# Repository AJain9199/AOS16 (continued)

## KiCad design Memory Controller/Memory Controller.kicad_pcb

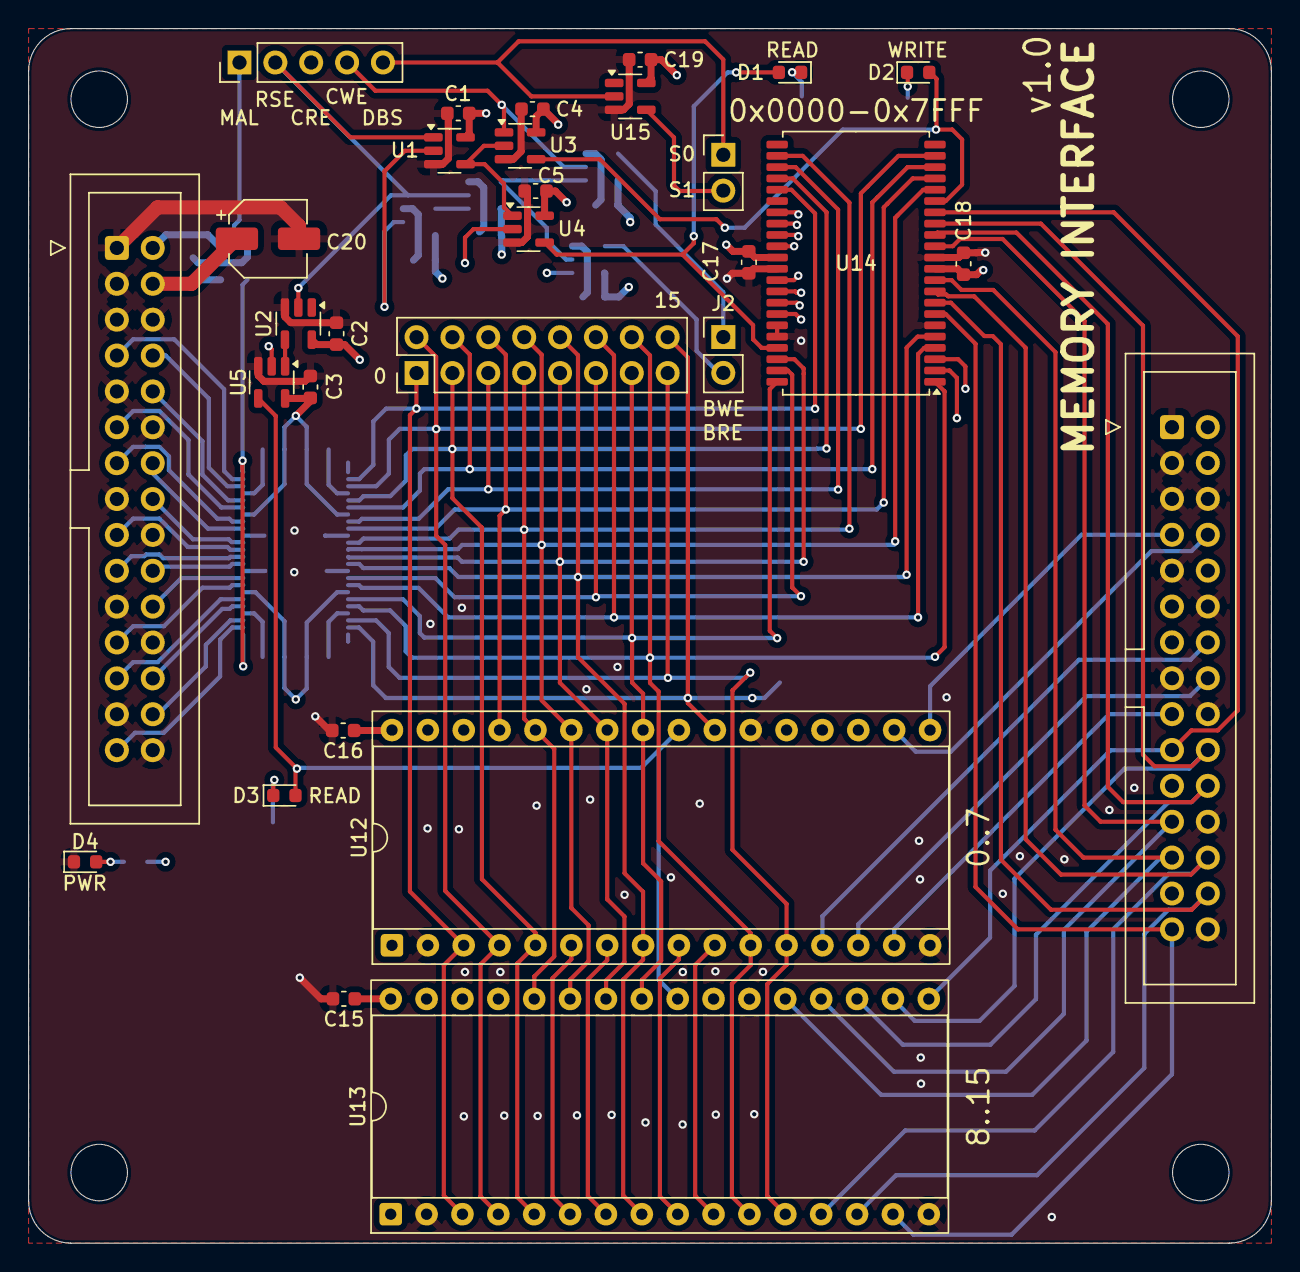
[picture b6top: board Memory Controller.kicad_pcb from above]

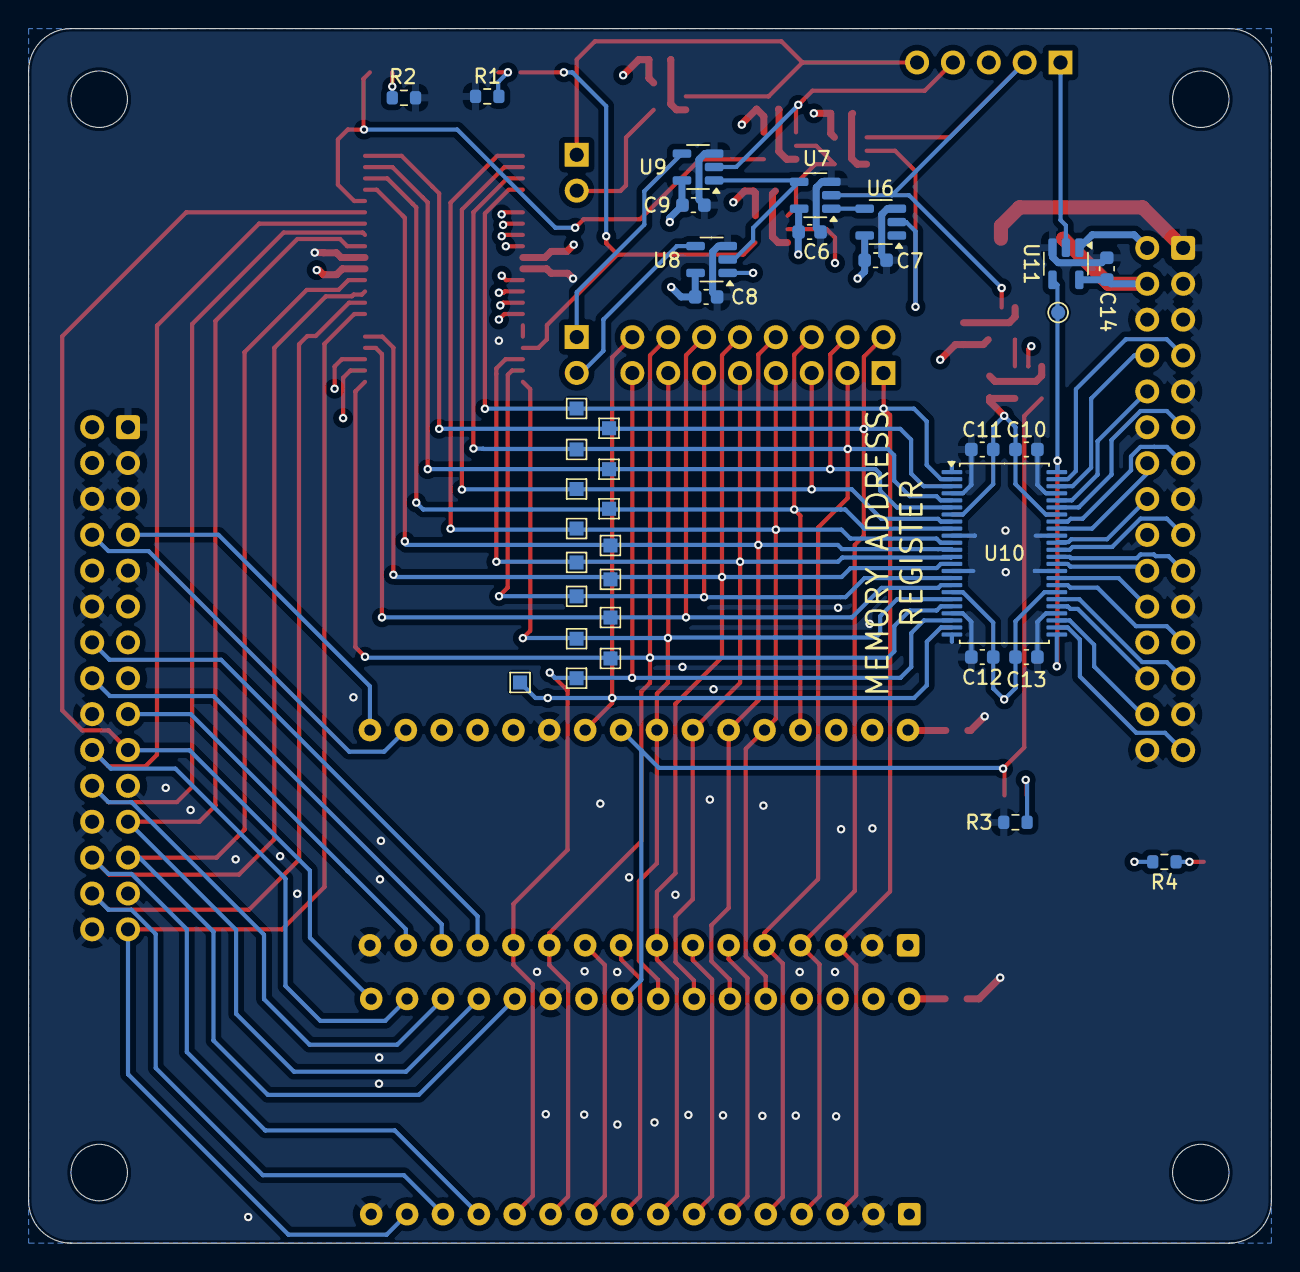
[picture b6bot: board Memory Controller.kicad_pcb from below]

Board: 4 copper layers, 88.0 x 86.0 mm, 70 parts (36 on the bottom side), 71 nets.

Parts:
C1, C2, C3, C4, C5, C6, C7, C8, C9, C15, C16, C19: C; C_0603_1608Metric
C10, C11, C12, C13: 0.01uF; C_0603_1608Metric
C14, C17, C18: 0.1uF; C_0603_1608Metric
C20: C; CP_Elec_5x5.3
D1, D2, D3, D4: LED; LED_0603_1608Metric
H1, H2, H3, H4: MountingHole; MountingHole_4mm
J1: Conn_01x05; PinHeader_1x05_P2.54mm_Vertical
J2, J6: Conn_01x02; PinHeader_1x02_P2.54mm_Vertical
J3, J5: Conn_02x15_Odd_Even; IDC-Header_2x15_P2.54mm_Vertical
J4: Conn_02x08_Top_Bottom; PinHeader_2x08_P2.54mm_Vertical
R1, R2, R3, R4: R; R_0603_1608Metric
TP1: TestPoint; TestPoint_Pad_D1.0mm
TP2, TP3, TP4, TP5, TP6, TP7, TP8, TP9, TP10, TP11, TP12, TP13, TP14, TP15, TP16, TP17: TestPoint_Small; TestPoint_Pad_1.0x1.0mm
U1, U3, U4, U5, U7, U8, U9: 74AHC1G32; SOT-23-5
U2, U6, U15: 74AHC1G04; SOT-23-5
U10: SN74AHCT16374DGGR; TSSOP-48_6.1x12.5mm_P0.5mm
U11: 74AHC1G08; SOT-23-5
U12, U13: SST39SF010; DIP-32_W15.24mm_Socket
U14: 71016S12PHG8; TSOP-II-44_10.16x18.41mm_P0.8mm

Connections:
+5V: C1.1, C2.1, C3.1, C4.1, C5.1, C6.1, C7.1, C8.1, C9.1, C10.1, C11.1, C12.1, C13.1, C14.1, C15.1, C16.1, C17.1, C18.1, C19.1, C20.1, J3.4, R4.2, U1.5 (VCC), U2.5 (VCC), U3.5 (VCC), U4.5 (VCC), U5.5 (VCC), U6.5 (VCC), U7.5 (VCC), U8.5 (VCC), U9.5 (VCC), U10.7 (VCC_1), U10.18 (VCC_2), U10.31 (VCC), U10.42 (VCC_4), U11.5 (VCC), U12.31 (PGM), U12.32 (VCC), U13.31 (PGM), U13.32 (VCC), U14.11 (VCC_1), U14.33 (VCC_2), U15.5 (VCC)
/BRE: J2.2, U8.4
/BWE: J2.1, U9.4
/CLK: J3.2, U11.1
/CRE: J1.3, U4.2, U5.2, U8.1
/CWE: J1.4, U3.1, U9.2
/DBS: J1.5, J6.1, U15.2
/MAL: J1.1, U11.2
/ROM/DATA0: J5.7, U12.17 (D3), U14.29 (I/O_8)
/ROM/DATA1: J5.8, U12.18 (D4), U14.30 (I/O_9)
/ROM/DATA2: J5.10, U12.19 (D5), U14.31 (I/O_10)
/ROM/DATA3: J5.11, U12.20 (D6), U14.32 (I/O_11)
/ROM/DATA4: J5.13, U12.21 (D7), U14.35 (I/O_12)
/ROM/DATA5: J5.14, U12.13 (D0), U14.36 (I/O_13)
/ROM/DATA6: J5.16, U12.14 (D1), U14.37 (I/O_14)
/ROM/DATA7: J5.17, U12.15 (D2), U14.38 (I/O_15)
/ROM/DATA8: J5.19, U13.17 (D3), U14.16 (I/O_7)
/ROM/DATA9: J5.20, U13.18 (D4), U14.15 (I/O_6)
/ROM/DATA10: J5.22, U13.19 (D5), U14.14 (I/O_5)
/ROM/DATA11: J5.23, U13.20 (D6), U14.13 (I/O_4)
/ROM/DATA12: J5.25, U13.21 (D7), U14.10 (I/O_3)
/ROM/DATA13: J5.26, U13.13 (D0), U14.9 (I/O_2)
/ROM/DATA14: J5.28, U13.14 (D1), U14.8 (I/O_1)
/ROM/DATA15: J5.29, U13.15 (D2), U14.7 (I/O_0)
/RSE: J1.2, U1.1, U2.2, U7.2
/S1: J6.2, U15.4
/bus_conn/IO0: J3.7, U10.47 (1D1)
/bus_conn/IO1: J3.8, U10.46 (1D2)
/bus_conn/IO2: J3.10, U10.44 (1D3)
/bus_conn/IO3: J3.11, U10.43 (1D4)
/bus_conn/IO4: J3.13, U10.41 (1D5)
/bus_conn/IO5: J3.14, U10.40 (1D6)
/bus_conn/IO6: J3.16, U10.38 (1D7)
/bus_conn/IO7: J3.17, U10.37 (1D8)
/bus_conn/IO8: J3.19, U10.36 (2D1)
/bus_conn/IO9: J3.20, U10.35 (2D2)
/bus_conn/IO10: J3.22, U10.33 (2D3)
/bus_conn/IO11: J3.23, U10.32 (2D4)
/bus_conn/IO12: J3.25, U10.30 (2D5)
/bus_conn/IO13: J3.26, U10.29 (2D6)
/bus_conn/IO14: J3.28, U10.27 (2D7)
/bus_conn/IO15: J3.29, U10.26 (2D8)
/word_conn/IN0: J4.1, TP2.1, U10.2 (1Q1), U12.3 (A15), U13.3 (A15), U14.27 (A8)
/word_conn/IN1: J4.2, TP3.1, U10.3 (1Q2), U12.4 (A12), U13.4 (A12), U14.21 (A12)
/word_conn/IN2: J4.3, TP4.1, U10.5 (1Q3), U12.5 (A7), U13.5 (A7), U14.26 (A9)
/word_conn/IN3: J4.4, TP5.1, U10.6 (1Q4), U12.6 (A6), U13.6 (A6), U14.20 (A13)
/word_conn/IN4: J4.5, TP6.1, U10.8 (1Q5), U12.7 (A5), U13.7 (A5), U14.25 (A10)
/word_conn/IN5: J4.6, TP7.1, U10.9 (1Q6), U12.29 (A14), U13.29 (A14), U14.19 (A14)
/word_conn/IN6: J4.7, TP8.1, U10.11 (1Q7), U12.28 (A13), U13.28 (A13), U14.24 (A11)
/word_conn/IN7: J4.8, TP9.1, U10.12 (1Q8), U12.27 (A8), U13.27 (A8), U14.18 (A15)
/word_conn/IN8: J4.9, TP10.1, U10.13 (2Q1), U12.26 (A9), U13.26 (A9), U14.42 (A7)
/word_conn/IN9: J4.10, TP11.1, U10.14 (2Q2), U12.8 (A4), U13.8 (A4), U14.5 (A0)
/word_conn/IN10: J4.11, TP12.1, U10.16 (2Q3), U12.9 (A3), U13.9 (A3), U14.43 (A6)
/word_conn/IN11: J4.12, TP13.1, U10.17 (2Q4), U12.10 (A2), U13.10 (A2), U14.4 (A1)
/word_conn/IN12: J4.13, TP14.1, U10.19 (2Q5), U12.25 (A11), U13.25 (A11), U14.44 (A5)
/word_conn/IN13: J4.14, TP15.1, U10.20 (2Q6), U12.11 (A1), U13.11 (A1), U14.1 (A4)
/word_conn/IN14: J4.15, TP16.1, U10.22 (2Q7), U12.12 (A0), U13.12 (A0), U14.3 (A2)
/word_conn/IN15: J4.16, TP17.1, U1.2, U6.2, U10.23 (2Q8), U12.23 (A10), U13.23 (A10), U14.2 (A3)
/~RAM_RE: D1.2 (A), U4.4, U14.41 (~OE)
/~RAM_WE: D2.2 (A), U3.4, U14.17 (~WE)
/~ROM_RE: D3.2 (A), U5.4, U12.24 (OE), U13.24 (OE)
GND: C1.2, C2.2, C3.2, C4.2, C5.2, C6.2, C7.2, C8.2, C9.2, C10.2, C11.2, C12.2, C13.2, C14.2, C15.2, C16.2, C17.2, C18.2, C19.2, C20.2, D4.1 (K), J3.1, J3.3, J3.5, J3.6, J3.9, J3.12, J3.15, J3.18, J3.21, J3.24, J3.27, J3.30, J5.1, J5.3, J5.5, J5.6, J5.9, J5.12, J5.15, J5.18, J5.21, J5.24, J5.27, J5.30, R1.1, R2.1, R3.1, U1.3 (GND), U2.3 (GND), U3.3 (GND), U4.3 (GND), U5.3 (GND), U6.3 (GND), U7.3 (GND), U8.3 (GND), U9.3 (GND), U10.1 (1~OE), U10.4 (GND_1), U10.10 (GND_2), U10.15 (GND_3), U10.21 (GND_4), U10.24 (2~OE), U10.28 (GND), U10.34 (GND_6), U10.39 (GND_7), U10.45 (GND_8), U11.3 (GND), U12.2 (A16), U12.16 (GND), U12.22 (CE), U13.2 (A16), U13.16 (GND), U13.22 (CE), U14.6 (~CS), U14.12 (VSS_1), U14.34 (VSS_2), U14.39 (~BLE), U14.40 (~BHE), U15.3 (GND)
unnamed: D1.1 (K), R1.2
unnamed: D2.1 (K), R2.2
unnamed: D3.1 (K), R3.2
unnamed: D4.2 (A), R4.1
unnamed: U1.4, U3.2, U4.1
unnamed: U2.4, U5.1
unnamed: U6.4, U7.1
unnamed: U7.4, U8.2, U9.1
unnamed: TP1.1, U10.25 (2CLK), U10.48 (1CLK), U11.4

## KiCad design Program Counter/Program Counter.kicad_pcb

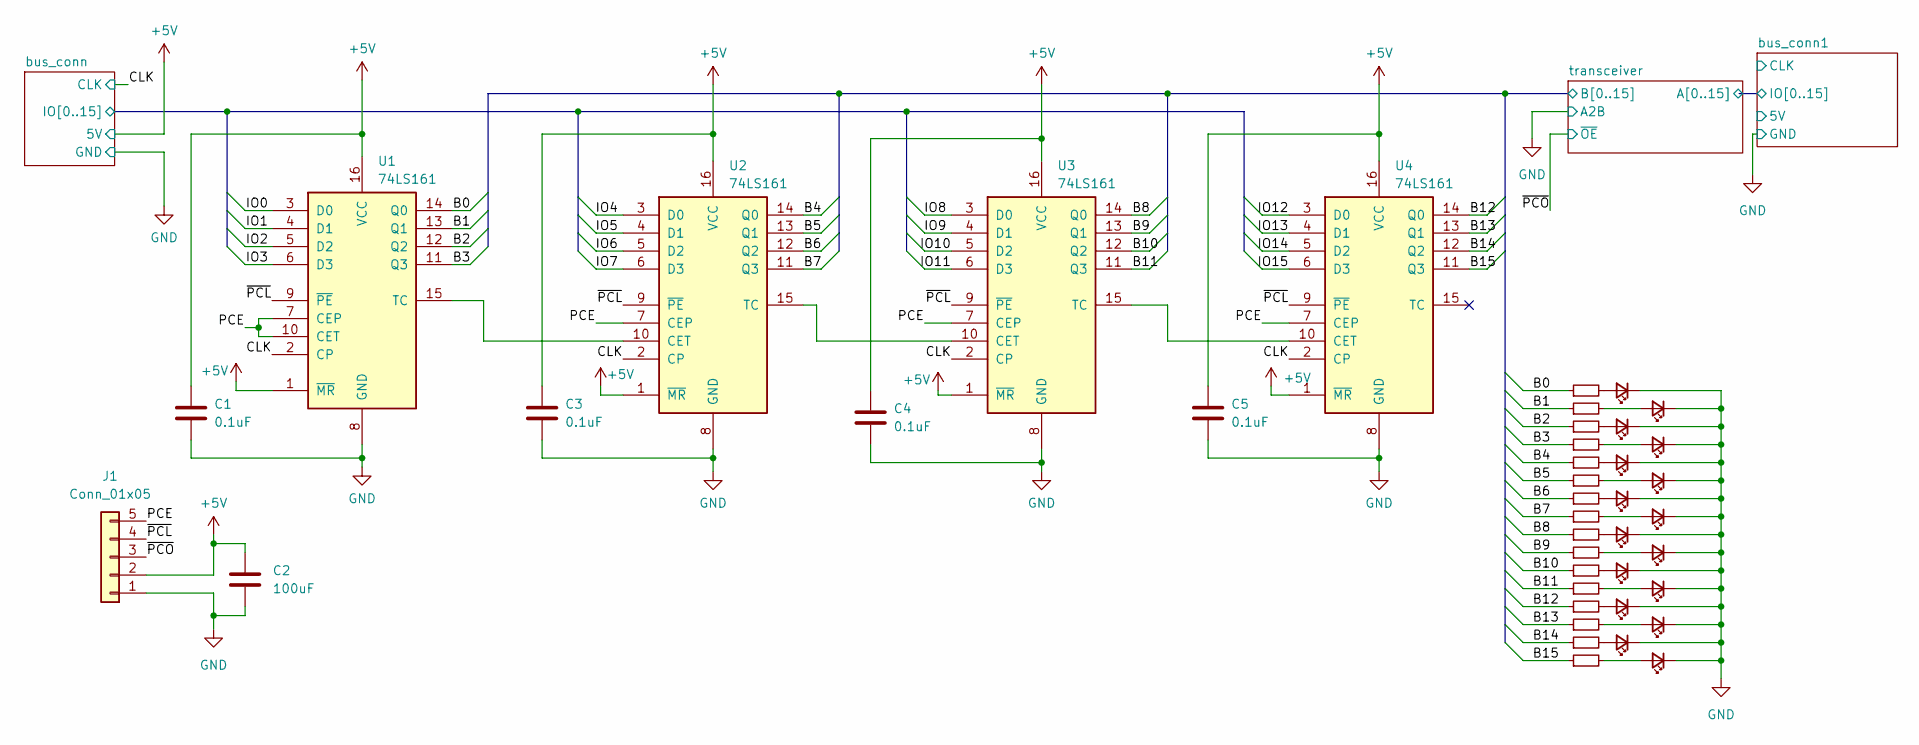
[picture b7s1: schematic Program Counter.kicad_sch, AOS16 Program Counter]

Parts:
C1, C3, C4, C5: 0.1uF; C_0603_1608Metric
C2: 100uF; CP_Elec_5x5.3
D1, D2, D3, D4, D5, D6, D7, D8, D9, D10, D11, D12, D13, D14, D15, D16: LED_Small; LED_0603_1608Metric
J1: Conn_01x05; PinHeader_1x05_P2.54mm_Vertical
R2, R3, R4, R5, R6, R7, R8, R9, R10, R11, R12, R13, R14, R15, R16, R17: 220; R_0603_1608Metric
U1, U2, U3, U4: 74LS161; SOIC-16_4.55x10.3mm_P1.27mm

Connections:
/CLK: U1.2 (CP), U2.2 (CP), U3.2 (CP), U4.2 (CP); also elsewhere on the board
/PCE: J1.5, U1.7 (CEP), U1.10 (CET), U2.7 (CEP), U3.7 (CEP), U4.7 (CEP)
/bus_conn/IO0: U1.3 (D0); also elsewhere on the board
/bus_conn/IO1: U1.4 (D1); also elsewhere on the board
/bus_conn/IO2: U1.5 (D2); also elsewhere on the board
/bus_conn/IO3: U1.6 (D3); also elsewhere on the board
/bus_conn/IO4: U2.3 (D0); also elsewhere on the board
/bus_conn/IO5: U2.4 (D1); also elsewhere on the board
/bus_conn/IO6: U2.5 (D2); also elsewhere on the board
/bus_conn/IO7: U2.6 (D3); also elsewhere on the board
/bus_conn/IO8: U3.3 (D0); also elsewhere on the board
/bus_conn/IO9: U3.4 (D1); also elsewhere on the board
/bus_conn/IO10: U3.5 (D2); also elsewhere on the board
/bus_conn/IO11: U3.6 (D3); also elsewhere on the board
/bus_conn/IO12: U4.3 (D0); also elsewhere on the board
/bus_conn/IO13: U4.4 (D1); also elsewhere on the board
/bus_conn/IO14: U4.5 (D2); also elsewhere on the board
/bus_conn/IO15: U4.6 (D3); also elsewhere on the board
/transceiver/B0: R2.1, U1.14 (Q0); also elsewhere on the board
/transceiver/B1: R3.1, U1.13 (Q1); also elsewhere on the board
/transceiver/B2: R4.1, U1.12 (Q2); also elsewhere on the board
/transceiver/B3: R5.1, U1.11 (Q3); also elsewhere on the board
/transceiver/B4: R6.1, U2.14 (Q0); also elsewhere on the board
/transceiver/B5: R7.1, U2.13 (Q1); also elsewhere on the board
/transceiver/B7: R9.1, U2.11 (Q3); also elsewhere on the board
/transceiver/B8: R10.1, U3.14 (Q0); also elsewhere on the board
/transceiver/B9: R11.1, U3.13 (Q1); also elsewhere on the board
/transceiver/B10: R12.1, U3.12 (Q2); also elsewhere on the board
/transceiver/B11: R13.1, U3.11 (Q3); also elsewhere on the board
/transceiver/B12: R14.1, U4.14 (Q0); also elsewhere on the board
/transceiver/B13: R15.1, U4.13 (Q1); also elsewhere on the board
/transceiver/B14: R16.1, U4.12 (Q2); also elsewhere on the board
/transceiver/B15: R17.1, U4.11 (Q3); also elsewhere on the board
/~PCL: J1.4, U1.9 (~PE), U2.9 (~PE), U3.9 (~PE), U4.9 (~PE)
GND: C1.2, C2.2, C3.2, C4.2, C5.2, D1.1 (K), D2.1 (K), D3.1 (K), D4.1 (K), D5.1 (K), D6.1 (K), D7.1 (K), D8.1 (K), D9.1 (K), D10.1 (K), D11.1 (K), D12.1 (K), D13.1 (K), D14.1 (K), D15.1 (K), D16.1 (K), J1.1, U1.8 (GND), U2.8 (GND), U3.8 (GND), U4.8 (GND); also elsewhere on the board
unnamed: D1.2 (A), R2.2
unnamed: D2.2 (A), R4.2
unnamed: D3.2 (A), R6.2
unnamed: D5.2 (A), R10.2
unnamed: D6.2 (A), R12.2
unnamed: D7.2 (A), R14.2
unnamed: D8.2 (A), R16.2
unnamed: D9.2 (A), R3.2
unnamed: D10.2 (A), R5.2
unnamed: D11.2 (A), R7.2
unnamed: D12.2 (A), R9.2
unnamed: D13.2 (A), R11.2
unnamed: D14.2 (A), R13.2
unnamed: D15.2 (A), R15.2
unnamed: D16.2 (A), R17.2
unnamed: U1.15 (TC), U2.10 (CET)
unnamed: U2.15 (TC), U3.10 (CET)
unnamed: U3.15 (TC), U4.10 (CET)

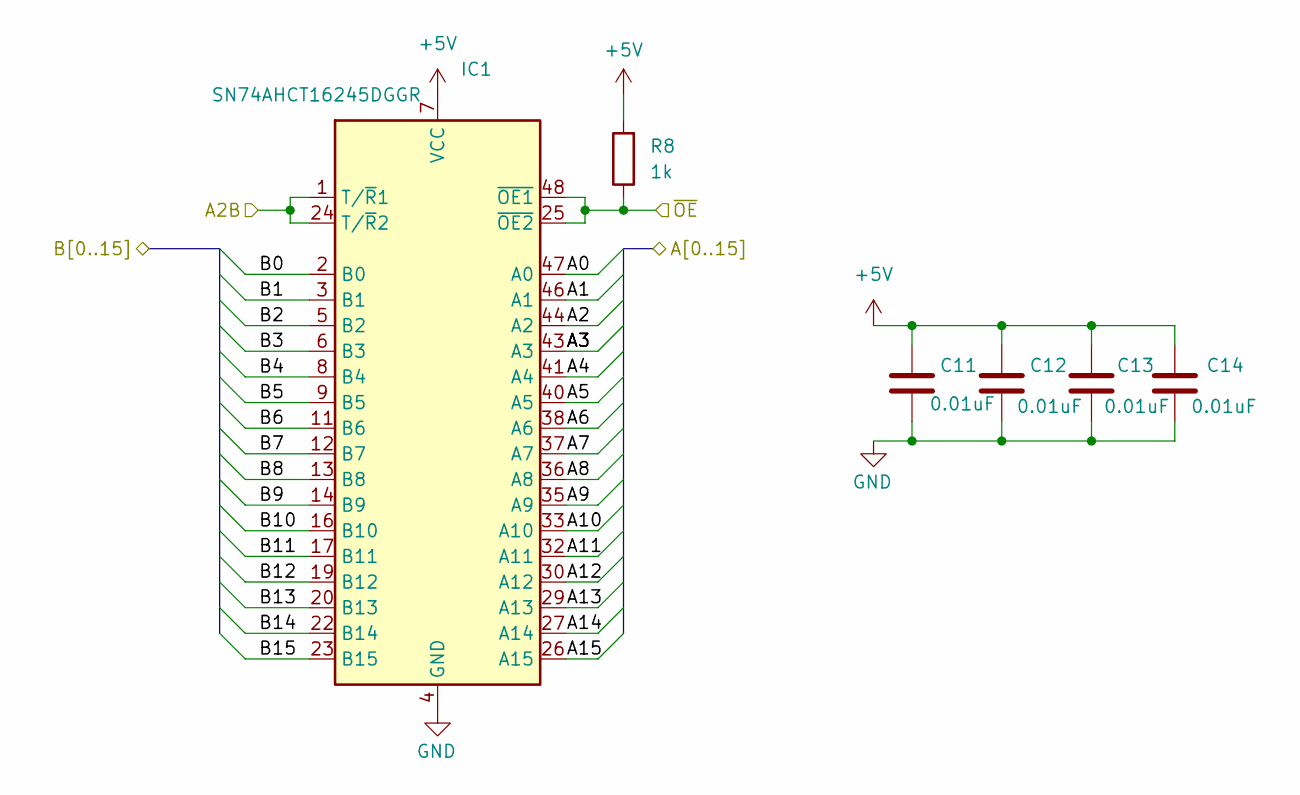
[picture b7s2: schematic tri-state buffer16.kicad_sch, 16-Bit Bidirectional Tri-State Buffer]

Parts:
C11, C12, C13, C14: 0.01uF; C_0603_1608Metric
IC1: SN74AHCT16245DGGR; TSSOP-48_6.1x12.5mm_P0.5mm
R8: 1k; R_0603_1608Metric

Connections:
/bus_conn1/IO0: IC1.47 (A0); also elsewhere on the board
/bus_conn1/IO1: IC1.46 (A1); also elsewhere on the board
/bus_conn1/IO2: IC1.44 (A2); also elsewhere on the board
/bus_conn1/IO3: IC1.43 (A3); also elsewhere on the board
/bus_conn1/IO4: IC1.41 (A4); also elsewhere on the board
/bus_conn1/IO5: IC1.40 (A5); also elsewhere on the board
/bus_conn1/IO6: IC1.38 (A6); also elsewhere on the board
/bus_conn1/IO7: IC1.37 (A7); also elsewhere on the board
/bus_conn1/IO8: IC1.36 (A8); also elsewhere on the board
/bus_conn1/IO9: IC1.35 (A9); also elsewhere on the board
/bus_conn1/IO10: IC1.33 (A10); also elsewhere on the board
/bus_conn1/IO11: IC1.32 (A11); also elsewhere on the board
/bus_conn1/IO12: IC1.30 (A12); also elsewhere on the board
/bus_conn1/IO13: IC1.29 (A13); also elsewhere on the board
/bus_conn1/IO14: IC1.27 (A14); also elsewhere on the board
/bus_conn1/IO15: IC1.26 (A15); also elsewhere on the board
/transceiver/B0: IC1.2 (B0); also elsewhere on the board
/transceiver/B1: IC1.3 (B1); also elsewhere on the board
/transceiver/B2: IC1.5 (B2); also elsewhere on the board
/transceiver/B3: IC1.6 (B3); also elsewhere on the board
/transceiver/B4: IC1.8 (B4); also elsewhere on the board
/transceiver/B5: IC1.9 (B5); also elsewhere on the board
/transceiver/B7: IC1.12 (B7); also elsewhere on the board
/transceiver/B8: IC1.13 (B8); also elsewhere on the board
/transceiver/B9: IC1.14 (B9); also elsewhere on the board
/transceiver/B10: IC1.16 (B10); also elsewhere on the board
/transceiver/B11: IC1.17 (B11); also elsewhere on the board
/transceiver/B12: IC1.19 (B12); also elsewhere on the board
/transceiver/B13: IC1.20 (B13); also elsewhere on the board
/transceiver/B14: IC1.22 (B14); also elsewhere on the board
/transceiver/B15: IC1.23 (B15); also elsewhere on the board
GND: C11.2, C12.2, C13.2, C14.2, IC1.1 (T/~R1), IC1.4 (GND), IC1.10 (GND), IC1.15 (GND), IC1.21 (GND), IC1.24 (T/~R2), IC1.28 (GND), IC1.34 (GND), IC1.39 (GND), IC1.45 (GND); also elsewhere on the board

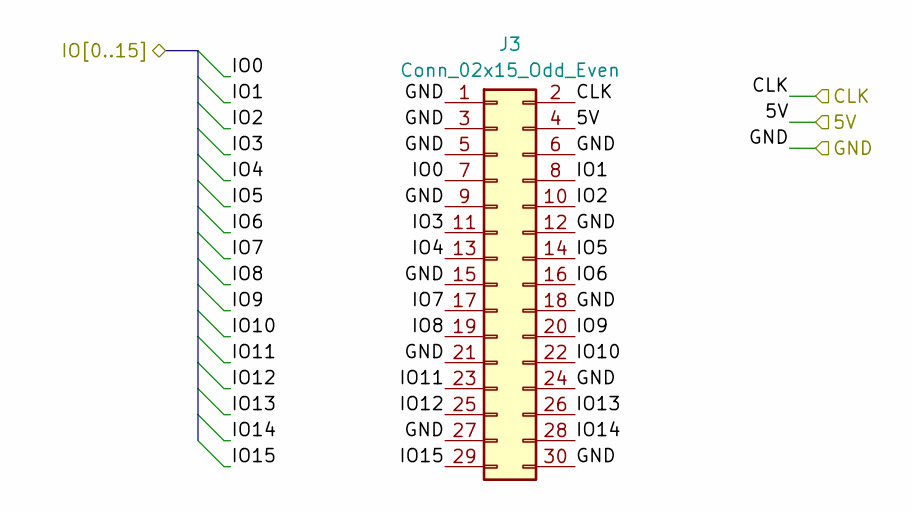
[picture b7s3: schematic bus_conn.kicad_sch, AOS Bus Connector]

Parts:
J3: Conn_02x15_Odd_Even; IDC-Header_2x15_P2.54mm_Vertical

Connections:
/bus_conn1/5V: J3.4
/bus_conn1/CLK: J3.2
/bus_conn1/IO0: J3.7; also elsewhere on the board
/bus_conn1/IO1: J3.8; also elsewhere on the board
/bus_conn1/IO2: J3.10; also elsewhere on the board
/bus_conn1/IO3: J3.11; also elsewhere on the board
/bus_conn1/IO4: J3.13; also elsewhere on the board
/bus_conn1/IO5: J3.14; also elsewhere on the board
/bus_conn1/IO6: J3.16; also elsewhere on the board
/bus_conn1/IO7: J3.17; also elsewhere on the board
/bus_conn1/IO8: J3.19; also elsewhere on the board
/bus_conn1/IO9: J3.20; also elsewhere on the board
/bus_conn1/IO10: J3.22; also elsewhere on the board
/bus_conn1/IO11: J3.23; also elsewhere on the board
/bus_conn1/IO12: J3.25; also elsewhere on the board
/bus_conn1/IO13: J3.26; also elsewhere on the board
/bus_conn1/IO14: J3.28; also elsewhere on the board
/bus_conn1/IO15: J3.29; also elsewhere on the board
GND: J3.1, J3.3, J3.5, J3.6, J3.9, J3.12, J3.15, J3.18, J3.21, J3.24, J3.27, J3.30; also elsewhere on the board

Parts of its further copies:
J2: Conn_02x15_Odd_Even; IDC-Header_2x15_P2.54mm_Vertical

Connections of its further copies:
/CLK: J2.2; also elsewhere on the board
/bus_conn/IO0: J2.7; also elsewhere on the board
/bus_conn/IO1: J2.8; also elsewhere on the board
/bus_conn/IO2: J2.10; also elsewhere on the board
/bus_conn/IO3: J2.11; also elsewhere on the board
/bus_conn/IO4: J2.13; also elsewhere on the board
/bus_conn/IO5: J2.14; also elsewhere on the board
/bus_conn/IO6: J2.16; also elsewhere on the board
/bus_conn/IO7: J2.17; also elsewhere on the board
/bus_conn/IO8: J2.19; also elsewhere on the board
/bus_conn/IO9: J2.20; also elsewhere on the board
/bus_conn/IO10: J2.22; also elsewhere on the board
/bus_conn/IO11: J2.23; also elsewhere on the board
/bus_conn/IO12: J2.25; also elsewhere on the board
/bus_conn/IO13: J2.26; also elsewhere on the board
/bus_conn/IO14: J2.28; also elsewhere on the board
/bus_conn/IO15: J2.29; also elsewhere on the board
GND: J2.1, J2.3, J2.5, J2.6, J2.9, J2.12, J2.15, J2.18, J2.21, J2.24, J2.27, J2.30; also elsewhere on the board

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
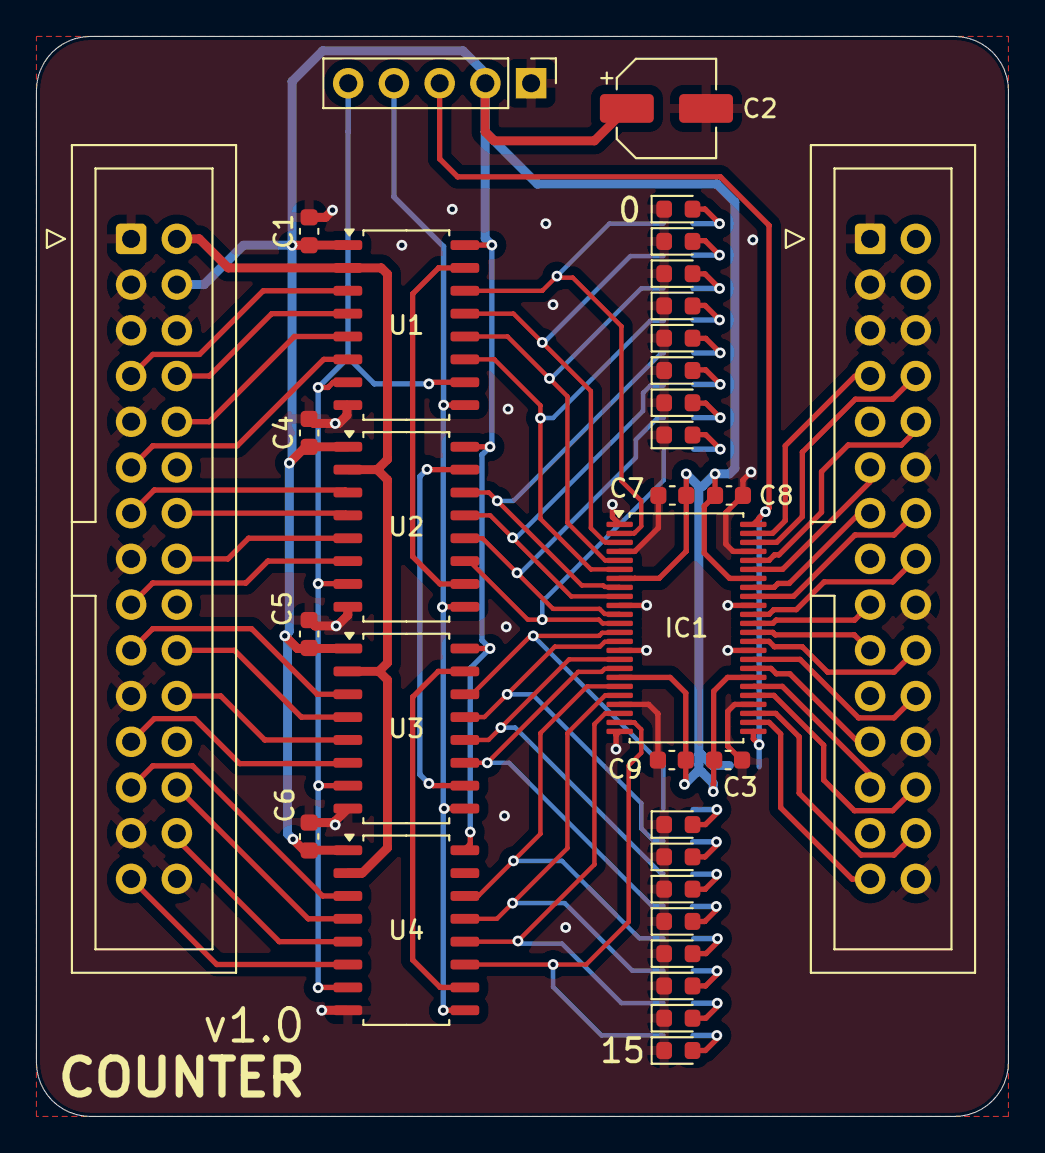
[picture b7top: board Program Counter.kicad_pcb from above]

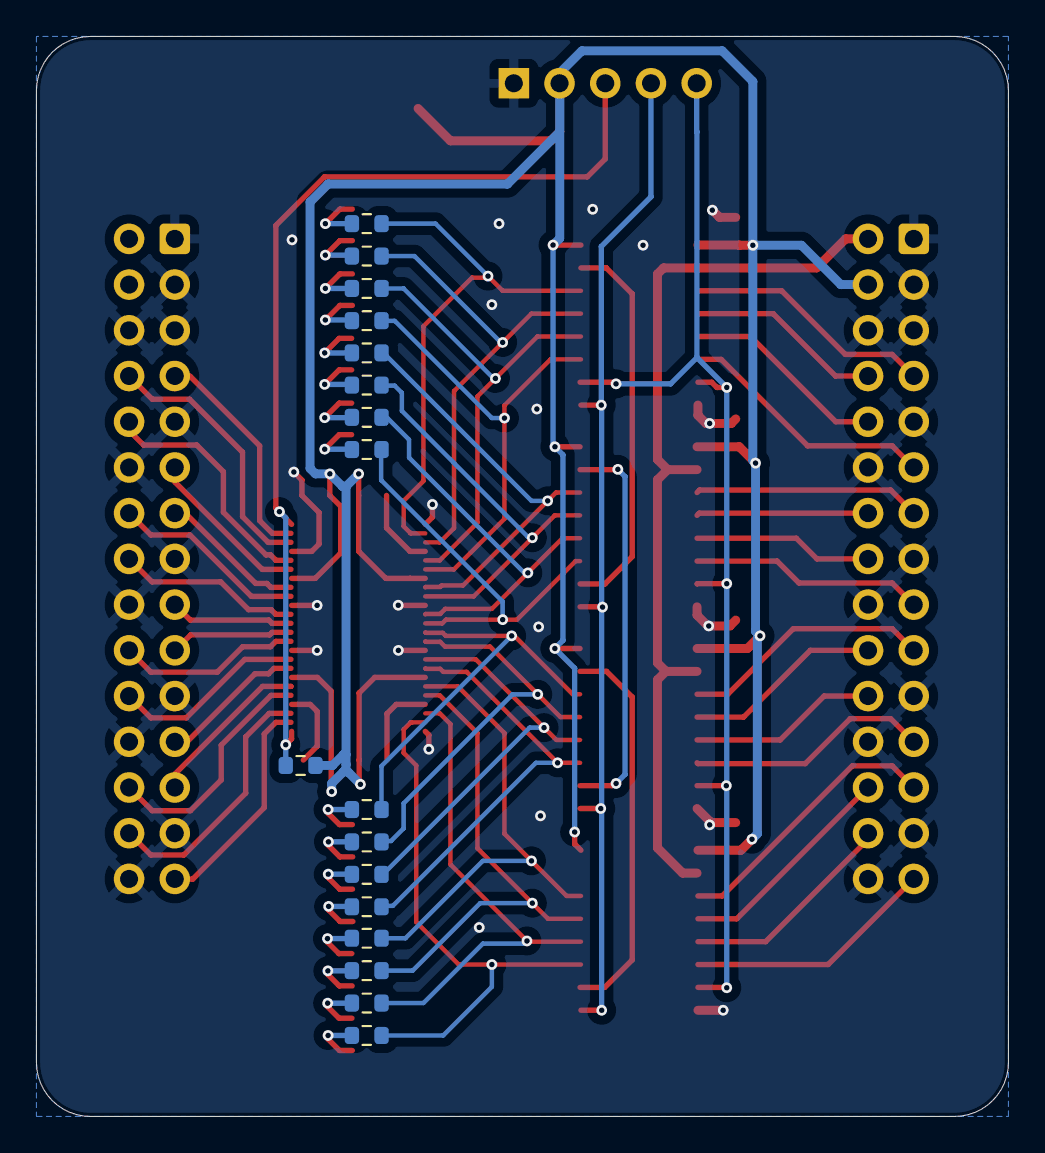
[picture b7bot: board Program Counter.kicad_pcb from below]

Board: 2 copper layers, 54.0 x 60.0 mm, 50 parts (17 on the bottom side), 73 nets.

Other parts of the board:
C6, C7, C8, C9: 0.01uF; C_0603_1608Metric
R18: 1k; R_0603_1608Metric

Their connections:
GND: C6.2, C7.2, C8.2, C9.2; also elsewhere on the board

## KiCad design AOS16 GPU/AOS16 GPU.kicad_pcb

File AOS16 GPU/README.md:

# AOS16 GPU

<h6 align="center">
GPU Front
</h6>

<h6 align="center">
GPU Back
</h6>

```mermaid
flowchart LR
    subgraph sub4 ["HCounter"]
        E["Counters"]
        F["Sync Comparator"]
        G["nOE Comparator"]
    end
    subgraph sub6 ["VCounter"]
        H["Counters"]
        I["Sync Comparator"]
        J["nOE Comparator"]
    end
    A[/"ADDR[0..14]"/]
    B[/"DATA[0..14]"/]
    C[["Digital-to-Analog<br/>Converter"]]
    D[/"VGA Output"/]
    K["NAND"]
    L(("nOE"))
    M(("CLK"))
    B --> C
    C -->|"RGB"| D
    E -->|"[0..7]"| A
    E --> F
    E --> G
    F -->|"HSync"| D
    H --> I
    H --> J
    I -->|"VSync"| D
    H -->|"[8..14]"| A
    G --> K
    J --> K
    K --> L
    M --> E
    M --> H
    %% mermaid-flow:pos E=333,36,76,32 F=467,104 G=465,161 H=668,45,80,32 I=815,97 J=816,158 A=115,260 B=101,362 C=298,363 D=561,403 K=595,264 L=820,341 M=77,55,101,60
```

## VGA Signal Generation
The board generates the SXGA 640x480@85Hz video mode. Each pixel is repeated 4 times across both axes for an effective resolution of 160x120. 

| Value                    | Frequency           |
| ------------------------ | ------------------- |
| Screen refresh rate      | 85 Hz               |
| Vertical refresh         | 43.269230769231 kHz |
| Pixel frequency          | 36.0 MHz            |
| **Clock frequency used** | **9.0 MHz**         |

It works by using counters for both the horizontal and vertical scanlines. The sync and output signals are set and unset at specific trigger counter values. 

### Horizontal Timing
2 [74hc161](../datasheets/sn74hc161.pdf)s are used to count the effective pixels. A quarter of the clock frequency (36/4 = 9 MHz) is used with the effective values to match the expected signal timings. Every line ending is used as the clock signal of the vertical counting circuit.

The 7 lower bits of the counter are used as ADDR\[0..7].

| Scanline Part         | Pixels | Effective Pixels | Time (µs) |
| --------------------- | ------ | ---------------- | --------- |
| Visible Area          | 640    | 120              | 17.777    |
| Front Porch           | 56     | 14               | 1.555     |
| Sync Pulse (inverted) | 56     | 14               | 1.555     |
| Back Porch            | 80     | 20               | 2.222     |
| Whole Line            | 832    | 208              | 23.111    |

### Vertical Timing
3 hc161s are used to count the actual lines. Bits \[2..8] are forwarded as the vertical address to ADDR\[8..14], effectively repeating each pixel 4 times.

| Frame Part   | Lines | Time (ms) |
| ------------ | ----- | --------- |
| Visible Area | 480   | 11.09333  |
| Front Porch  | 1     | 0.02311   |
| Sync Pulse   | 3     | 0.06933   |
| Back Porch   | 25    | 0.577     |
| Full Frame   | 509   | 11.76355  |
|              |       |           |
## Linear Framebuffer Mapping

| Dimension  | Value          |
| ---------- | -------------- |
| Width      | 160px          |
| Height     | 120px          |
| Pitch      | 256 words      |
| Depth      | 5 bits / color |
| Pixelwidth | 1 word         |
```c
uint16_t *pixel = 0x7FFF + y*pitch + x
```

## Test Video

https://github.com/user-attachments/assets/5f555ebd-57f7-4c56-b4e2-e7593a60e567

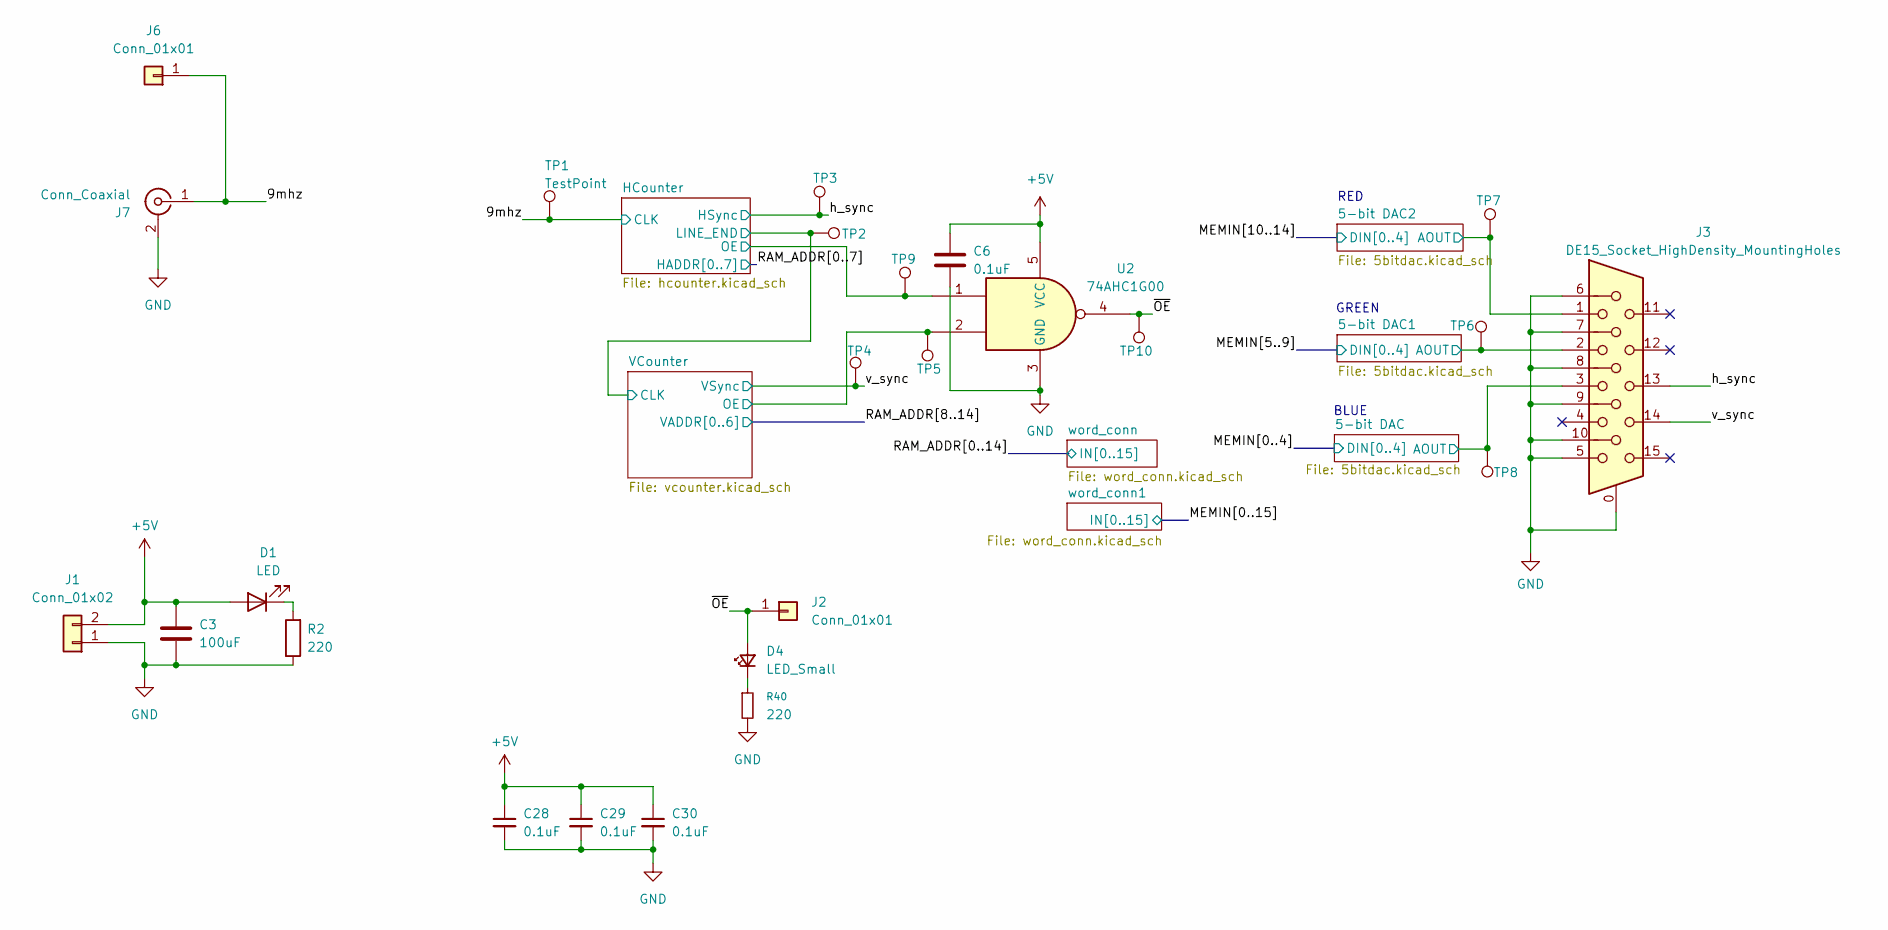
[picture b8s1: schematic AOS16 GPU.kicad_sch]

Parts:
C3: 100uF; CP_Elec_5x5.3
C6, C28, C29, C30: 0.1uF; C_0603_1608Metric
D1: LED; LED_0603_1608Metric
D4: LED_Small; LED_0603_1608Metric
J1: Conn_01x02; PinHeader_1x02_P2.54mm_Vertical
J2, J6: Conn_01x01; PinHeader_1x01_P2.54mm_Vertical
J3: DE15_Socket_HighDensity_MountingHoles; DSUB-15-HD_Socket_Horizontal_P2.29x1.90mm_EdgePinOffset3.03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
J7: Conn_Coaxial; SMA_Amphenol_132289_EdgeMount
R2, R40: 220; R_0603_1608Metric
TP1, TP2, TP3, TP4, TP5, TP6, TP7, TP8, TP9, TP10: TestPoint; TestPoint_Pad_D2.0mm
U2: 74AHC1G00; SOT-23-5

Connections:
+5V: C3.1, C6.1, C28.1, C29.1, C30.1, D1.2 (A), J1.2, U2.5 (VCC); also elsewhere on the board
/5-bit DAC1/AOUT: J3.2, TP6.1; also elsewhere on the board
/5-bit DAC2/AOUT: J3.1, TP7.1; also elsewhere on the board
/5-bit DAC/AOUT: J3.3, TP8.1; also elsewhere on the board
/9mhz: J6.1, J7.1 (In), TP1.1; also elsewhere on the board
/HCounter/OE: TP9.1, U2.1; also elsewhere on the board
/HCounter/~READ SET: TP2.1; also elsewhere on the board
/VCounter/OE: TP5.1, U2.2; also elsewhere on the board
/h_sync: J3.13, TP3.1; also elsewhere on the board
/v_sync: J3.14, TP4.1; also elsewhere on the board
/~OE: D4.2 (A), J2.1, TP10.1, U2.4
GND: C3.2, C6.2, C28.2, C29.2, C30.2, J1.1, J3.0, J3.5, J3.6, J3.7, J3.8, J3.9, J3.10, J7.2 (Ext), R2.1, R40.2, U2.3 (GND); also elsewhere on the board
unnamed: D1.1 (K), R2.2
unnamed: D4.1 (K), R40.1

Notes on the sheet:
RED
BLUE
GREEN
